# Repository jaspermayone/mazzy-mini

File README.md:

# mazzy mini

A small KiCad PCB for probing and mapping the factory wiring harness of a Mazda vehicle using a Metra 70-7903 pigtail adapter.

## What it does

The board plugs into the factory harness via Metra 70-7903 pigtail ([the one we ordered](https://a.co/d/05tSerNA), 24-pin + 16-pin connectors) and provides:

- **40 through-hole solder/probe pads** (TP1–TP24 for the 24-pin side, TP25–TP40 for the 16-pin side) — one pad per Metra pigtail wire, labeled with known wire color/function or UNKNOWN for unidentified signals. These pads are intended to be soldered to the pigtail wires, not mated as removable connectors.
- **SN65HVD230 CAN transceiver** on 3.3V, wired to CAN_TX/CAN_RX for a Raspberry Pi Pico 2 W (GP4/GP5) to sniff and identify the Mazda MS-CAN bus by jumper-probing the unknown pads.
- **CANH/CANL screw terminal** (J1, Phoenix 1725656) plus CANH/CANL probe pads (TP45/TP46) for jumpering candidate harness wires onto the bus while identifying MS-CAN.
- **Onboard 3.3V LDO** (AMS1117-3.3) fed from a user-selectable BAT12 (constant) or ACC12 (switched) source via JP1 solder jumper.
- **P-channel MOSFET reverse-polarity protection** (PMV100EPAR, Q1) with a 15V gate-source zener clamp, plus a unidirectional SMBJ15A TVS clamp on the 12V input before the regulator.
- **Optional CAN termination** (120Ω R4 across CANH/CANL, **DNP** by default) — leave unpopulated on the already-terminated Mazda factory MS-CAN bus.
- **3.3V power LED** (D1) for quick confirmation that JP1 and the 12V input path are live.
- **USB-C 5V input rail** (J5 receptacle with 5.1kΩ CC pull-downs, ESD TVS, and ferrite bead to 5V_USB) exposed to the Pico header for bench Pico power. It does **not** currently feed the AMS1117/onboard 3V3 rail.
- **Pico 3V3 isolation jumper** (JP3) keeps Pico-facing 3.3V header pins isolated from onboard 3V3 by default to avoid regulator backfeed/fighting.
- **Rail/debug probe pads** — TP41 (3V3), TP42 (5V_USB), TP43 (VIN12), TP44 (GND), TP45 (CANH), TP46 (CANL).

## Known wires (24-pin side)

| Pad | Wire | Function |
|-----|------|----------|
| TP1 | Green | BAT12 — constant 12V+ |
| TP2 | Gray | ACC12 — switched 12V+ |
| TP3 | Black | Ground |
| TP4 | White | Front-left speaker + |
| TP5 | Yellow | Front-left speaker − |
| TP6 | Red | Front-right speaker + |
| TP7 | Blue | Front-right speaker − |
| TP8 | White | Rear-left speaker + |
| TP9 | Light green | Rear-left speaker − |
| TP10 | Blue | Rear-right speaker + |
| TP11 | Brown | Rear-right speaker − |
| TP12–TP24 | — | UNKNOWN — map during probing |

TP25–TP40 are the 16-pin pigtail side; all currently UNKNOWN.

## Schematic source

The schematic is defined in Python using [SKiDL](https://github.com/devbisme/skidl) in `circuit.py`. Running it generates the netlist used by KiCad.

```
pip install skidl
python circuit.py
```

The KiCad project files (`circuit.kicad_sch`, `circuit.kicad_pcb`, etc.) are the primary design artifacts and are checked in alongside the source.

## JP1 — power source selection

Solder jumper JP1 selects whether the onboard 3.3V regulator is fed from BAT12 (always on) or ACC12 (ignition-switched). Leave it **open** while mapping unknown harness pins so the board is only powered intentionally.

## R4 — CAN termination (DNP)

R4 (120Ω across CANH/CANL) is marked **do not populate**. The Mazda factory MS-CAN bus is already terminated at both ends. Only fit R4 if you are running a standalone bench test with no other termination present.

## JP3 — Pico 3V3 isolation

Leave **open** by default. J4's 3.3V pin is on `PICO_3V3`, isolated from the onboard AMS1117 `3V3` rail unless JP3 is bridged. This prevents the Pico regulator and onboard regulator from backfeeding each other. Bridge JP3 only when you intentionally want one selected 3.3V source to power both sides.

## USB-C power limitation

`5V_USB` is routed to the Pico-facing header and its probe pad only. It does not diode-OR into the AMS1117 input, so USB-C alone will not power U1/the onboard CAN transceiver unless a future power-OR stage is added.

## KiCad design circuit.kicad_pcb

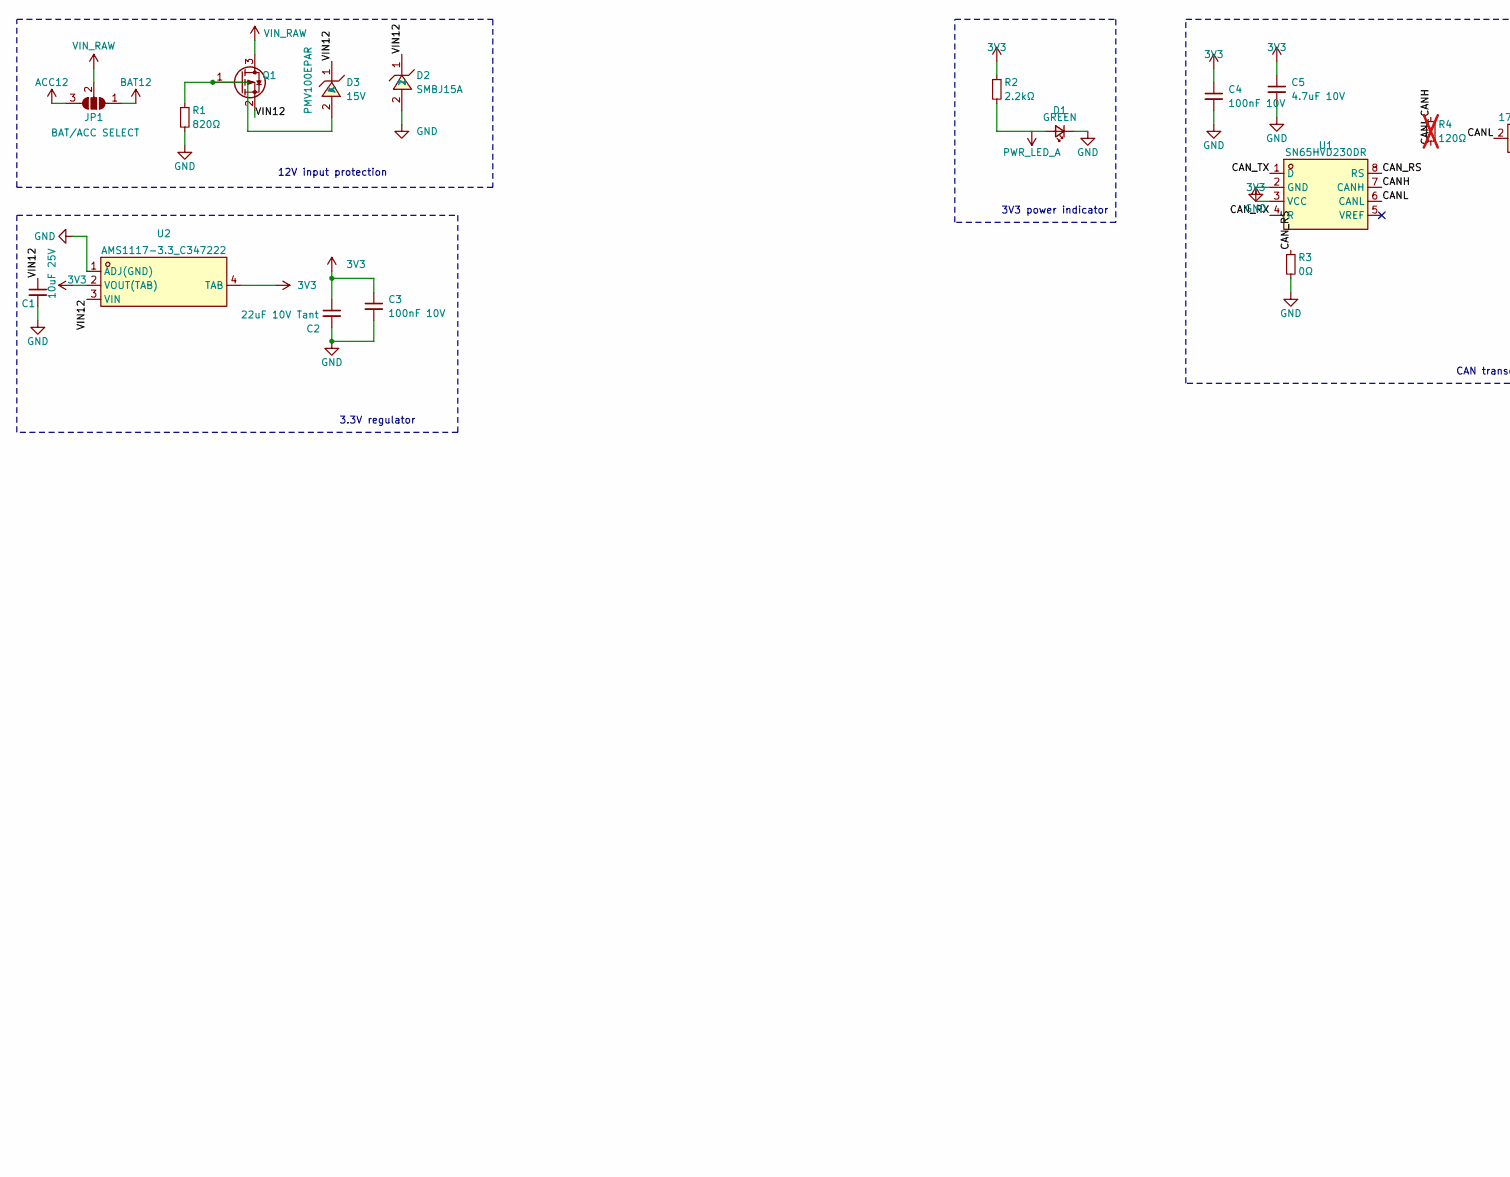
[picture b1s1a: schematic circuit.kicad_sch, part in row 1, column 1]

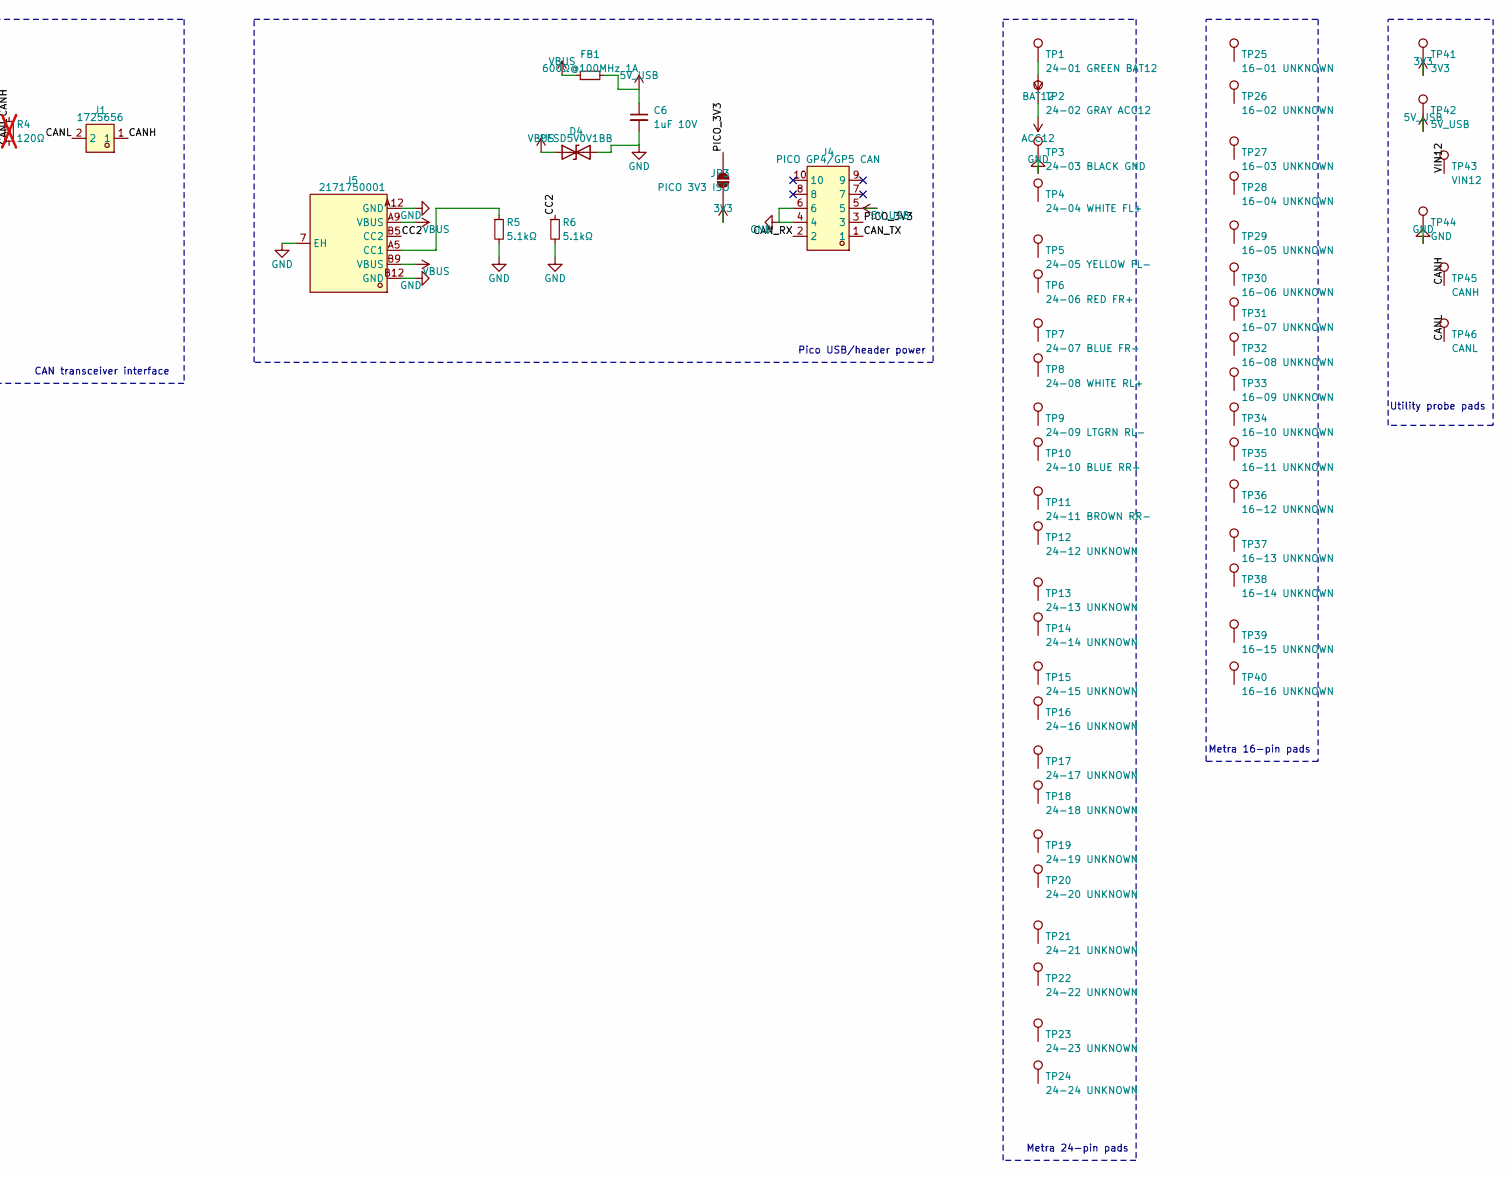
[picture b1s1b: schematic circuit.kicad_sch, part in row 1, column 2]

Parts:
C1: 10uF 25V; C_1206_3216Metric; LCSC Part NONE
C2: 22uF 10V Tant; CP_EIA-3528-21_Kemet-B_HandSolder; LCSC Part NONE
C3, C4: 100nF 10V; C_0603_1608Metric; LCSC Part NONE
C5: 4.7uF 10V; C_0805_2012Metric; LCSC Part NONE
C6: 1uF 10V; C_0603_1608Metric; LCSC Part NONE
D1: GREEN; LED_0603_1608Metric; LCSC Part C20433785
D2: SMBJ15A; SMB_L4.6-W3.6-LS5.3-RD; LCSC Part C83846
D3: 15V; SOD-123_L2.7-W1.6-LS3.7-RD; LCSC Part C129730
D4: PESD5V0V1BB; SOD-523_L1.2-W0.8-LS1.6-RD; LCSC Part C477993
FB1: 600Ω@100MHz 1A; R_0603_1608Metric; LCSC Part C404396
J1: 1725656; CONN-TH_2P-P2.54_1725656; LCSC Part C3029316
J4: PICO GP4/GP5 CAN; HDR-TH_10P-P2.54-V-M-R2-C5-S2.54; LCSC Part C586266
J5: 2171750001; TYPE-C-SMD_TYPE-C-6P_USB4125-GF-A-0190; LCSC Part C3197922
JP1: BAT/ACC SELECT; SolderJumper-3_P2.0mm_Open_TrianglePad1.0x1.5mm; LCSC Part NONE
JP3: PICO 3V3 ISO; SolderJumper-2_P1.3mm_Open_RoundedPad1.0x1.5mm; LCSC Part NONE
Q1: PMV100EPAR; SOT-23-3_L2.9-W1.3-P1.90-LS2.3-BR; LCSC Part C3290636
R1: 820Ω; R_0603_1608Metric; LCSC Part NONE
R2: 2.2kΩ; R_0603_1608Metric; LCSC Part NONE
R3: 0Ω; R_0603_1608Metric; LCSC Part NONE
R4: 120Ω; R_0805_2012Metric; LCSC Part NONE; not fitted
R5, R6: 5.1kΩ; R_0603_1608Metric; LCSC Part NONE
TP1: 24-01 GREEN BAT12; TestPoint_THTPad_D2.5mm_Drill1.2mm; LCSC Part NONE
TP2: 24-02 GRAY ACC12; TestPoint_THTPad_D2.5mm_Drill1.2mm; LCSC Part NONE
TP3: 24-03 BLACK GND; TestPoint_THTPad_D2.5mm_Drill1.2mm; LCSC Part NONE
TP4: 24-04 WHITE FL+; TestPoint_THTPad_D2.5mm_Drill1.2mm; LCSC Part NONE
TP5: 24-05 YELLOW FL-; TestPoint_THTPad_D2.5mm_Drill1.2mm; LCSC Part NONE
TP6: 24-06 RED FR+; TestPoint_THTPad_D2.5mm_Drill1.2mm; LCSC Part NONE
TP7: 24-07 BLUE FR-; TestPoint_THTPad_D2.5mm_Drill1.2mm; LCSC Part NONE
TP8: 24-08 WHITE RL+; TestPoint_THTPad_D2.5mm_Drill1.2mm; LCSC Part NONE
TP9: 24-09 LTGRN RL-; TestPoint_THTPad_D2.5mm_Drill1.2mm; LCSC Part NONE
TP10: 24-10 BLUE RR+; TestPoint_THTPad_D2.5mm_Drill1.2mm; LCSC Part NONE
TP11: 24-11 BROWN RR-; TestPoint_THTPad_D2.5mm_Drill1.2mm; LCSC Part NONE
TP12: 24-12 UNKNOWN; TestPoint_THTPad_D2.5mm_Drill1.2mm; LCSC Part NONE
TP13: 24-13 UNKNOWN; TestPoint_THTPad_D2.5mm_Drill1.2mm; LCSC Part NONE
TP14: 24-14 UNKNOWN; TestPoint_THTPad_D2.5mm_Drill1.2mm; LCSC Part NONE
TP15: 24-15 UNKNOWN; TestPoint_THTPad_D2.5mm_Drill1.2mm; LCSC Part NONE
TP16: 24-16 UNKNOWN; TestPoint_THTPad_D2.5mm_Drill1.2mm; LCSC Part NONE
TP17: 24-17 UNKNOWN; TestPoint_THTPad_D2.5mm_Drill1.2mm; LCSC Part NONE
TP18: 24-18 UNKNOWN; TestPoint_THTPad_D2.5mm_Drill1.2mm; LCSC Part NONE
TP19: 24-19 UNKNOWN; TestPoint_THTPad_D2.5mm_Drill1.2mm; LCSC Part NONE
TP20: 24-20 UNKNOWN; TestPoint_THTPad_D2.5mm_Drill1.2mm; LCSC Part NONE
TP21: 24-21 UNKNOWN; TestPoint_THTPad_D2.5mm_Drill1.2mm; LCSC Part NONE
TP22: 24-22 UNKNOWN; TestPoint_THTPad_D2.5mm_Drill1.2mm; LCSC Part NONE
TP23: 24-23 UNKNOWN; TestPoint_THTPad_D2.5mm_Drill1.2mm; LCSC Part NONE
TP24: 24-24 UNKNOWN; TestPoint_THTPad_D2.5mm_Drill1.2mm; LCSC Part NONE
TP25: 16-01 UNKNOWN; TestPoint_THTPad_D2.5mm_Drill1.2mm; LCSC Part NONE
TP26: 16-02 UNKNOWN; TestPoint_THTPad_D2.5mm_Drill1.2mm; LCSC Part NONE
TP27: 16-03 UNKNOWN; TestPoint_THTPad_D2.5mm_Drill1.2mm; LCSC Part NONE
TP28: 16-04 UNKNOWN; TestPoint_THTPad_D2.5mm_Drill1.2mm; LCSC Part NONE
TP29: 16-05 UNKNOWN; TestPoint_THTPad_D2.5mm_Drill1.2mm; LCSC Part NONE
TP30: 16-06 UNKNOWN; TestPoint_THTPad_D2.5mm_Drill1.2mm; LCSC Part NONE
TP31: 16-07 UNKNOWN; TestPoint_THTPad_D2.5mm_Drill1.2mm; LCSC Part NONE
TP32: 16-08 UNKNOWN; TestPoint_THTPad_D2.5mm_Drill1.2mm; LCSC Part NONE
TP33: 16-09 UNKNOWN; TestPoint_THTPad_D2.5mm_Drill1.2mm; LCSC Part NONE
TP34: 16-10 UNKNOWN; TestPoint_THTPad_D2.5mm_Drill1.2mm; LCSC Part NONE
TP35: 16-11 UNKNOWN; TestPoint_THTPad_D2.5mm_Drill1.2mm; LCSC Part NONE
TP36: 16-12 UNKNOWN; TestPoint_THTPad_D2.5mm_Drill1.2mm; LCSC Part NONE
TP37: 16-13 UNKNOWN; TestPoint_THTPad_D2.5mm_Drill1.2mm; LCSC Part NONE
TP38: 16-14 UNKNOWN; TestPoint_THTPad_D2.5mm_Drill1.2mm; LCSC Part NONE
TP39: 16-15 UNKNOWN; TestPoint_THTPad_D2.5mm_Drill1.2mm; LCSC Part NONE
TP40: 16-16 UNKNOWN; TestPoint_THTPad_D2.5mm_Drill1.2mm; LCSC Part NONE
TP41: 3V3; TestPoint_THTPad_D2.0mm_Drill1.0mm; LCSC Part NONE
TP42: 5V_USB; TestPoint_THTPad_D2.0mm_Drill1.0mm; LCSC Part NONE
TP43: VIN12; TestPoint_THTPad_D2.0mm_Drill1.0mm; LCSC Part NONE
TP44: GND; TestPoint_THTPad_D2.0mm_Drill1.0mm; LCSC Part NONE
TP45: CANH; TestPoint_THTPad_D2.0mm_Drill1.0mm; LCSC Part NONE
TP46: CANL; TestPoint_THTPad_D2.0mm_Drill1.0mm; LCSC Part NONE
U1: SN65HVD230DR; SOIC-8_L4.9-W3.9-P1.27-LS6.0-BL; LCSC Part C12084
U2: AMS1117-3.3_C347222; SOT-223-4_L6.5-W3.5-P2.30-LS7.0-BR; LCSC Part C347222

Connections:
3V3: C2.1, C3.1, C4.1, C5.1, JP3.1 (A), R2.1, TP41.1, U1.3 (VCC), U2.2 (VOUT(TAB)), U2.4 (TAB)
5V_USB: C6.1, FB1.2, J4.5, TP42.1
ACC12: JP1.3 (B), TP2.1
BAT12: JP1.1 (A), TP1.1
CANH: J1.1, R4.1, TP45.1, U1.7 (CANH)
CANL: J1.2, R4.2, TP46.1, U1.6 (CANL)
CAN_RS: R3.1, U1.8 (RS)
CAN_RX: J4.2, U1.4 (R)
CAN_TX: J4.1, U1.1 (D)
CC1: J5.A5 (CC1), R5.1
CC2: J5.B5 (CC2), R6.1
FL_SPK_N: TP5.1
FL_SPK_P: TP4.1
FR_SPK_N: TP7.1
FR_SPK_P: TP6.1
GND: C1.2, C2.2, C3.2, C4.2, C5.2, C6.2, D1.1 (K), D2.2, D4.2 (A2), J4.4, J4.6, J5.7 (EH), J5.A12 (GND), J5.B12 (GND), R1.2, R3.2, R5.2, R6.2, TP3.1, TP44.1, U1.2 (GND), U2.1 (ADJ(GND))
H16_01: TP25.1
H16_02: TP26.1
H16_03: TP27.1
H16_04: TP28.1
H16_05: TP29.1
H16_06: TP30.1
H16_07: TP31.1
H16_08: TP32.1
H16_09: TP33.1
H16_10: TP34.1
H16_11: TP35.1
H16_12: TP36.1
H16_13: TP37.1
H16_14: TP38.1
H16_15: TP39.1
H16_16: TP40.1
H24_12: TP12.1
H24_13: TP13.1
H24_14: TP14.1
H24_15: TP15.1
H24_16: TP16.1
H24_17: TP17.1
H24_18: TP18.1
H24_19: TP19.1
H24_20: TP20.1
H24_21: TP21.1
H24_22: TP22.1
H24_23: TP23.1
H24_24: TP24.1
PICO_3V3: J4.3, JP3.2 (B)
PWR_LED_A: D1.2 (A), R2.2
RL_SPK_N: TP9.1
RL_SPK_P: TP8.1
RP_GATE: D3.2 (A), Q1.1 (G), R1.1
RR_SPK_N: TP11.1
RR_SPK_P: TP10.1
VBUS: D4.1 (A1), FB1.1, J5.A9 (VBUS), J5.B9 (VBUS)
VIN12: C1.1, D2.1, D3.1 (K), Q1.2 (S), TP43.1, U2.3 (VIN)
VIN_RAW: JP1.2 (C), Q1.3 (D)

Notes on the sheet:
CAN transceiver interface
12V input protection
Pico USB/header power
3V3 power indicator
Metra 16-pin pads
3.3V regulator
Metra 24-pin pads
Utility probe pads

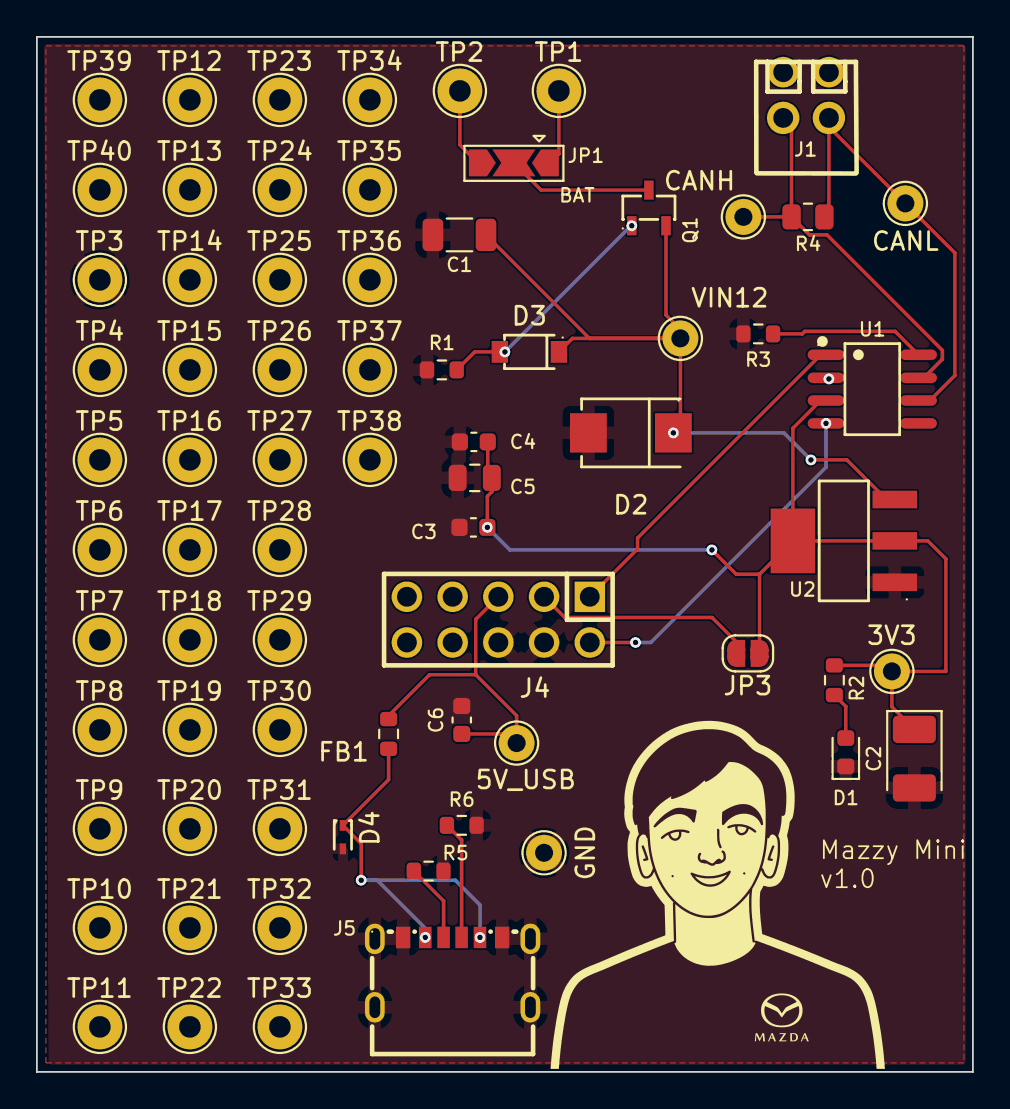
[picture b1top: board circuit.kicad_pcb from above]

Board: 2 copper layers, 52.0 x 57.5 mm, 71 parts (0 on the bottom side), 18 nets.

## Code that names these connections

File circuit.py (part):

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    # satisfies KiCad ERC power_pin_not_driven without changing connectivity.
    pwr_flag_rails = [
        (1, gnd, "Ground enters via the Metra black harness wire (TP3) and USB-C shell/GND pins."),
        (2, bat12, "Constant 12V enters via the Metra green harness wire on TP1."),
        (3, acc12, "Switched 12V enters via the Metra gray harness wire on TP2."),
        (4, vin12, "Protected 12V rail driven through Q1 reverse-polarity MOSFET (passive path)."),
        (5, vbus, "5V enters from the USB-C connector J5 VBUS pins."),
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    # The supplied community documentation gives functions/wire colors, but not a verified
    # OEM cavity-number map. Keep the physical labels tied to the pigtail wire colors.
    harness_pads = [
        (1, "24-01 GREEN BAT12", bat12, "24-pin Metra pigtail pad for green battery constant 12V+ wire."),
        (2, "24-02 GRAY ACC12", acc12, "24-pin Metra pigtail pad for gray accessory switched 12V+ wire."),
        (3, "24-03 BLACK GND", gnd, "24-pin Metra pigtail pad for black ground wire."),
        (4, "24-04 WHITE FL+", Net("FL_SPK_P"), "24-pin Metra pigtail pad for front-left speaker positive, white wire."),
        (5, "24-05 YELLOW FL-", Net("FL_SPK_N"), "24-pin Metra pigtail pad for front-left speaker negative, yellow wire."),
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        footprint="Jumper:SolderJumper-3_P2.0mm_Open_TrianglePad1.0x1.5mm",
    )
    jp1.lcsc = "NONE"
    jp1.info = "Open 3-pad solder jumper used to select BAT12 or ACC12 as the source for the onboard 3.3V regulator; leave open while mapping unknown harness pins."
    design_intent(
        jp1,
        "Selects whether the onboard 3.3V regulator is fed from BAT12 constant power or ACC12 switched power; no bridge by default for safe harness mapping.",
        group="12V input selection and protection",
        placement="Place next to TP1/TP2 and label center pad VIN, side pads BAT and ACC.",
    )
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        footprint="Library:SOD-123_L2.7-W1.6-LS3.7-RD",
    )
    d3.lcsc = "C129730"
    d3.info = "onsemi MMSZ5245BT1G 15V 500mW zener, SOD-123. Pin 1 cathode to Q1 source/VIN12, pin 2 anode to Q1 gate/RP_GATE; clamps PMOS VGS around -15V and below the +/-20V rating."
    design_intent(
        d3,
        "Gate-source zener clamp for Q1 so positive VIN12/source spikes cannot overdrive the PMOS gate oxide.",
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
    d2 = Part("Library", "SMBJ15A_C83846", value="SMBJ15A", ref="D2", footprint="Library:SMB_L4.6-W3.6-LS5.3-RD")
    d2.lcsc = "C83846"
    d2.info = "Littelfuse SMBJ15A unidirectional TVS: pin 1 cathode/banded side to VIN12, pin 2 anode to GND; 15V VRWM, 16.7V min breakdown, 24.4V clamp at 24.6A. This is transient suppression, not full ISO automotive load-dump qualification for AMS1117."
    design_intent(
        d2,
        "Unidirectional 15V TVS clamp across the protected 12V rail to shunt positive harness spikes without clamping normal positive polarity.",
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        footprint="Library:SOIC-8_L4.9-W3.9-P1.27-LS6.0-BL",
    )
    u1.lcsc = "C12084"
    u1.info = "TI SN65HVD230DR: pin1 D/TXD, pin2 GND, pin3 VCC, pin4 R/RXD, pin5 VREF may float if unused, pin6 CANL, pin7 CANH, pin8 RS. ICC max 17mA dominant; RS low selects high-speed mode."
    design_intent(
        u1,
        "3.3V CAN transceiver used with Raspberry Pi Pico 2 W GP4/GP5 to identify Mazda MS-CAN H/L by jumper-probing unknown harness pads.",
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        footprint="Jumper:SolderJumper-2_P1.3mm_Open_RoundedPad1.0x1.5mm",
    )
    jp3.lcsc = "NONE"
    jp3.info = "Normally-open solder jumper between onboard 3V3 and Pico-facing PICO_3V3 header pins. Leave open by default to avoid backfeeding/fighting the Pico 3.3V regulator; bridge only when one 3.3V source is intentionally selected."
    design_intent(
        jp3,
        "Optional bridge from onboard 3V3 to Pico-facing 3.3V header pins; open by default for backfeed protection.",
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    j1.info = "2-position Phoenix Contact 1725656 2.54mm screw terminal exposing CANH and CANL."
    design_intent(
        j1,
        "2-pin screw terminal exposing CANH and CANL for jumper wires to unknown harness pads or for using an external Waveshare SN65HVD230 module instead of U1.",
        group="CAN transceiver and probe headers",
        placement="Put on board edge, label pin 1 CANH and pin 2 CANL.",
    )
    canh += j1[1]
    canl += j1[2]
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        footprint="Library:HDR-TH_10P-P2.54-V-M-R2-C5-S2.54",
    )
    j4.lcsc = "C586266"
    j4.info = "10-pin 2.54mm Pico utility header exposing GP4/CAN_TX, GP5/CAN_RX, isolated PICO_3V3, GND, and USB 5V. PICO_3V3 is not tied to onboard 3V3 unless JP3 is bridged."
    design_intent(
        j4,
        "10-pin Pico utility header exposing CAN_TX for GP4, CAN_RX for GP5, isolated PICO_3V3, GND, and USB 5V for direct Pico 2 W jumper access.",
        group="Pico power and logic headers",
        placement="Place near board edge with silk: 1 GP4/TX, 2 GP5/RX, 3 P3V3, 4 GND, 5 5V_USB, 6 GND.",
    )
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        (42, "5V_USB", v5usb, "USB-C 5V probe/header rail; not generated from vehicle 12V."),
        (43, "VIN12", vin12, "Protected selected 12V rail after Q1 reverse-polarity MOSFET."),
        (44, "GND", gnd, "Ground probe pad tied to the Metra black ground wire and USB-C ground."),
        (45, "CANH", canh, "CANH probe pad tied to U1 and J1 pin 1; jumper candidate harness wires here while identifying MS-CAN."),
        (46, "CANL", canl, "CANL probe pad tied to U1 and J1 pin 2; jumper candidate harness wires here while identifying MS-CAN."),
    ]
    for rail_num, rail_label, rail_net, rail_intent in rail_points:
        rail_tp = Part(
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
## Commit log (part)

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2026-06-29 inital commit
2026-06-29 (karl) updates
2026-06-29 small updates
2026-06-29 add readme
2026-06-30 progress
